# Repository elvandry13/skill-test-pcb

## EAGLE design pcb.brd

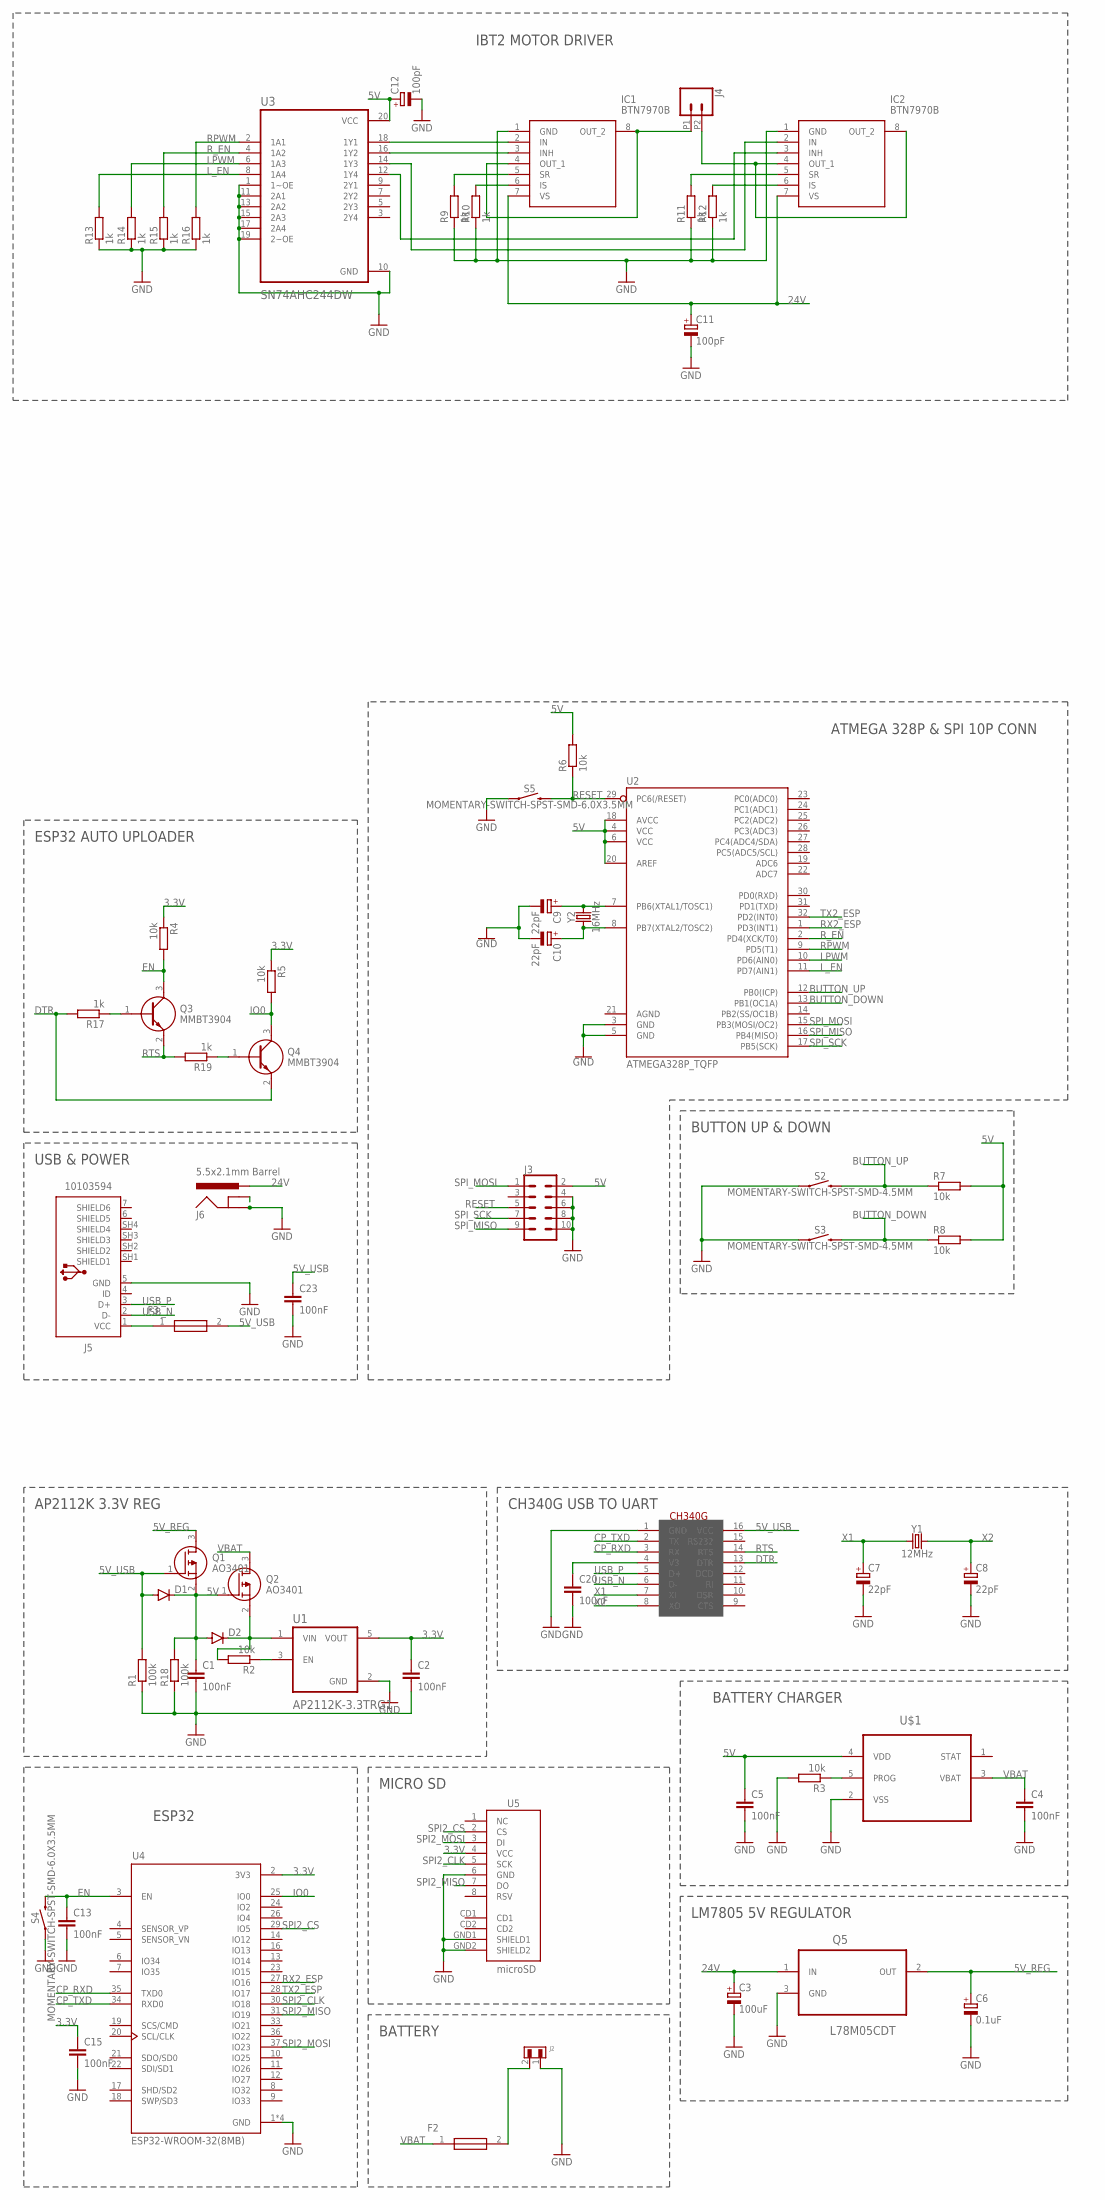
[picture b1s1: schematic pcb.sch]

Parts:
C1, C2, C4, C5, C13, C15, C20, C23: 100nF; C0603
C3: 100uF; SMC_C
C6: 0.1uF; SMC_C
C7, C8, C9, C10: 22pF; SMC_C
C11, C12: 100pF; SMC_C
D1, D2: DIODE-DO214AC; DO214AC
F2, F3: MF-NSML260_12-2; FUSC3216X100N
IC1, IC2: BTN7970B; PG-TO263-7-1
J2: 620102131822
J3: CONN_05X2SHD-NS; 2X5-SHROUDED-NS
J4: CONN_022.54MM_SCREWTERM; 1X02_2.54_SCREWTERM
J5: 10103594
J6: 5.5x2.1mm Barrel; POWER_JACK_SMD
Q1, Q2: AO3401; SOT95P280X125-3N
Q3, Q4: MMBT3904; SOT95P240X120-3N
Q5: L78M05CDT; TO225P972X240-3N
R1, R18: 100k; R0603
R2, R3, R4, R5, R6, R7, R8: 10k; R0603
R9, R10, R11, R12, R13, R14, R15, R16, R17, R19: 1k; R0603
S2, S3: MOMENTARY-SWITCH-SPST-SMD-4.5MM; TACTILE_SWITCH_SMD_4.5MM
S4, S5: MOMENTARY-SWITCH-SPST-SMD-6.0X3.5MM; TACTILE_SWITCH_SMD_6.0X3.5MM
U1: AP2112K-3.3TRG1; SOT95P285X140-5N
U2: ATMEGA328P_TQFP; TQFP32-08
U3: SN74AHC244DW; SOIC127P1030X265-20N
U4: ESP32-WROOM-32(8MB); MODULE_ESP32-WROOM-32(8MB)
U5: microSD; MICRO-SD-SOCKET-PP
U$1: MCP73831T-5ACI/OT; SOT95P280X145-5N
U$2: CH340G; SOIC16
Y1: 12MHz; CRYSTAL-SMD-5X3.2-4PAD
Y2: 16MHz; CRYSTAL-SMD-5X3.2-4PAD

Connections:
3.3V: C2.1, C15.1, R4.1, R5.1, U1.5 (VOUT), U4.2 (3V3), U5.4 (VCC)
5V: C1.1, C5.1, C12.+, D1.C, D2.A, J3.2, Q1.2 (S), Q2.1 (G), R6.2, R7.2, R8.2, R18.2, U2.4 (VCC), U2.6 (VCC), U2.18 (AVCC), U2.20 (AREF), U3.20 (VCC), U$1.4 (VDD)
5V_REG: C6.+, Q1.3 (D), Q5.2 (OUT)
5V_USB: C23.1, D1.A, F3.2, Q1.1 (G), R1.2, U$2.16 (VCC)
24V: C3.+, C11.+, IC1.7 (VS), IC2.7 (VS), J6.VIN0 (PWR), Q5.1 (IN)
BUTTON_DOWN: R8.1, S3.1 (2), S3.4 (2), U2.13 (PB1(OC1A))
BUTTON_UP: R7.1, S2.1 (2), S2.4 (2), U2.12 (PB0(ICP))
CP_RXD: U4.35 (TXD0), U$2.3 (RX)
CP_TXD: U4.34 (RXD0), U$2.2 (TX)
DTR: Q4.2 (E), R17.2, U$2.13 (DTR)
EN: C13.1, Q3.3 (C), R4.2, S4.2, U4.3 (EN)
GND: C1.2, C2.2, C3.-, C4.2, C5.2, C6.-, C7.-, C8.-, C9.-, C10.-, C11.-, C12.-, C13.2, C15.2, C20.2, C23.2, IC1.1 (GND), IC2.1 (GND), J2.1, J3.4, J3.6, J3.8, J3.10, J5.5 (GND), J6.P$4 (GND), Q5.3 (GND), R1.1, R3.2, R9.1, R10.1, R11.1, R12.1, R13.1, R14.1, R15.1, R16.1, R18.1, S2.2 (1), S2.3 (1), S3.2 (1), S3.3 (1), S4.1, S5.1, U1.2 (GND), U2.3 (GND), U2.5 (GND), U3.1 (1~OE), U3.10 (GND), U3.11 (2A1), U3.13 (2A2), U3.15 (2A3), U3.17 (2A4), U3.19 (2~OE), U4.1 (GND), U4.15 (GND), U4.38 (GND), U4.39 (GND), U5.6 (GND), U5.GND1 (SHIELD1), U5.GND2 (SHIELD2), U$1.2 (VSS), U$2.1 (GND)
IO0: Q4.3 (C), R5.2, U4.25 (IO0)
LPWM: R14.2, U2.10 (PD6(AIN0)), U3.6 (1A3)
L_EN: R13.2, U2.11 (PD7(AIN1)), U3.8 (1A4)
unnamed: D2.C, Q2.2 (S), R2.2, U1.1 (VIN)
unnamed: IC1.4 (OUT_1), IC1.8 (OUT_2), J4.P1 (1)
unnamed: C9.+, U2.7 (PB6(XTAL1/TOSC1)), Y2.3 (2)
unnamed: R2.1, U1.3 (EN)
unnamed: R3.1, U$1.5 (PROG)
unnamed: C10.+, U2.8 (PB7(XTAL2/TOSC2)), Y2.1
unnamed: IC2.4 (OUT_1), IC2.8 (OUT_2), J4.P2 (2)
unnamed: IC1.5 (SR), R9.2
unnamed: IC1.2 (IN), U3.18 (1Y1)
unnamed: IC1.3 (INH), U3.16 (1Y2)
unnamed: IC1.6 (IS), R10.2
unnamed: IC2.2 (IN), U3.14 (1Y3)
unnamed: IC2.3 (INH), U3.12 (1Y4)
unnamed: IC2.5 (SR), R11.2
unnamed: C20.1, U$2.4 (V3)
unnamed: IC2.6 (IS), R12.2
unnamed: F3.1, J5.1 (VCC)
unnamed: Q3.1 (B), R17.1
unnamed: Q4.1 (B), R19.1
unnamed: F2.2, J2.2
RESET: J3.5, R6.1, S5.2, U2.29 (PC6(/RESET))
RPWM: R16.2, U2.9 (PD5(T1)), U3.2 (1A1)
RTS: Q3.2 (E), R19.2, U$2.14 (RTS)
RX2_ESP: U2.1 (PD3(INT1)), U4.27 (IO16)
R_EN: R15.2, U2.2 (PD4(XCK/T0)), U3.4 (1A2)
SPI2_CLK: U4.30 (IO18), U5.5 (SCK)
SPI2_CS: U4.29 (IO5), U5.2 (CS)
SPI2_MISO: U4.31 (IO19), U5.7 (DO)
SPI2_MOSI: U4.37 (IO23), U5.3 (DI)
SPI_MISO: J3.9, U2.16 (PB4(MISO))
SPI_MOSI: J3.1, U2.15 (PB3(MOSI/OC2))
SPI_SCK: J3.7, U2.17 (PB5(SCK))
TX2_ESP: U2.32 (PD2(INT0)), U4.28 (IO17)
USB_N: J5.2 (D-), U$2.6 (D-)
USB_P: J5.3 (D+), U$2.5 (D+)
VBAT: C4.1, F2.1, Q2.3 (D), U$1.3 (VBAT)
X1: C7.+, U$2.7 (XI), Y1.1
X2: C8.+, U$2.8 (XO), Y1.3 (2)

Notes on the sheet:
BATTERY
AP2112K 3.3V REG
ESP32
LM7805 5V REGULATOR
BATTERY CHARGER
USB & POWER
MICRO SD
CH340G USB TO UART
ESP32 AUTO UPLOADER
BUTTON UP & DOWN
ATMEGA 328P & SPI 10P CONN
IBT2 MOTOR DRIVER

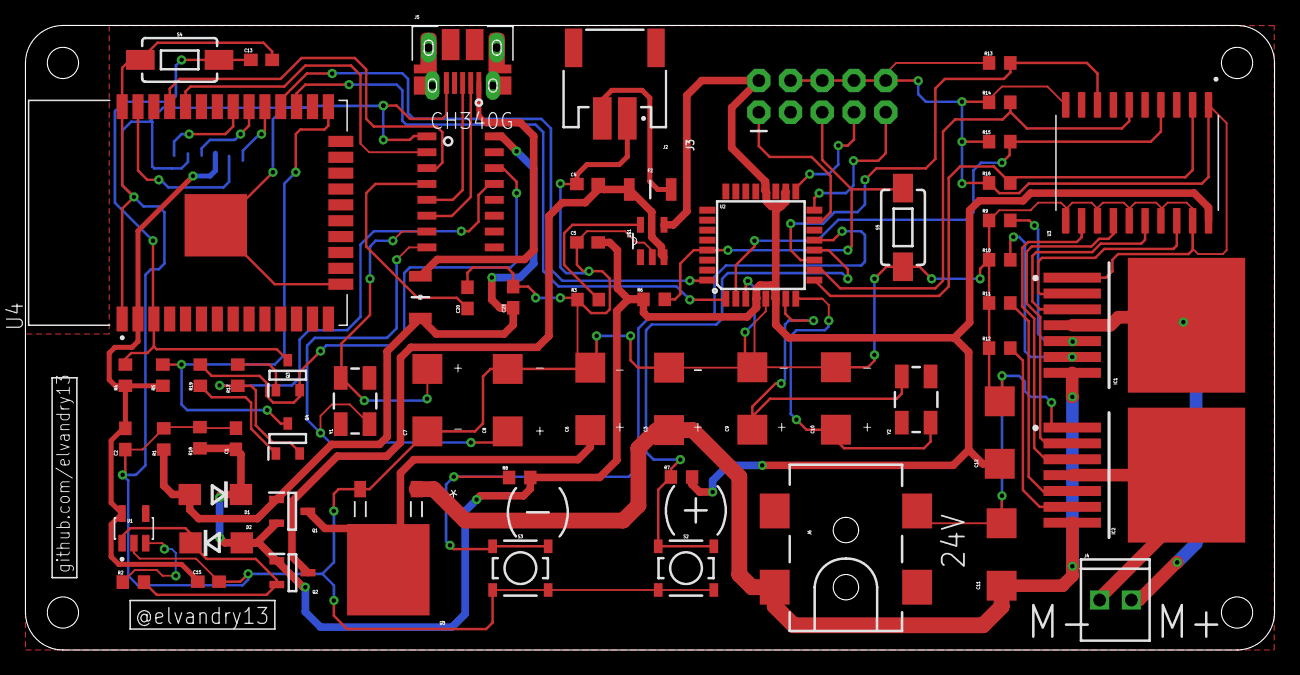
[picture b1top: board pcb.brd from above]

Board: 4 copper layers, 100.0 x 50.0 mm, 64 parts (1 on the bottom side), 53 nets.

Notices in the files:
parts and their libraries:
Wurth_Connectors_WR-WTB: Copyright: Würth Elektronik
SparkFun-Clocks: Licensing: Creative Commons ShareAlike 4.0 International - https://creativecommons.org/licenses/by-sa/4.0
